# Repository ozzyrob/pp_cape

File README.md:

# pp_cape

Beaglebone Black cape to breakout signals to a 26 pin header

Intent is to replicate order of Parallel Port (not function)
to facilitate migration from x86 Linuxcnc users to BBB Machinekit
users

  * Port 1 header has 8 Outputs + 5 Inputs + 4 Outputs
  * Port 2 header has 8 Inputs + 5 Inputs + 4 Outputs
  * Pin 26 on each header is an "enable pin"
  * I2C is broken out to a 1x4 pin header (SCL SDL 3v3 DGND)
  * P9.1 to P9.10 are broken out to a 2x4 pin header
  * ADC Inputs and ADC ground are broken out (reference has not been)

To be used in conjunction with pp_bob_output & pp_bob_input boards

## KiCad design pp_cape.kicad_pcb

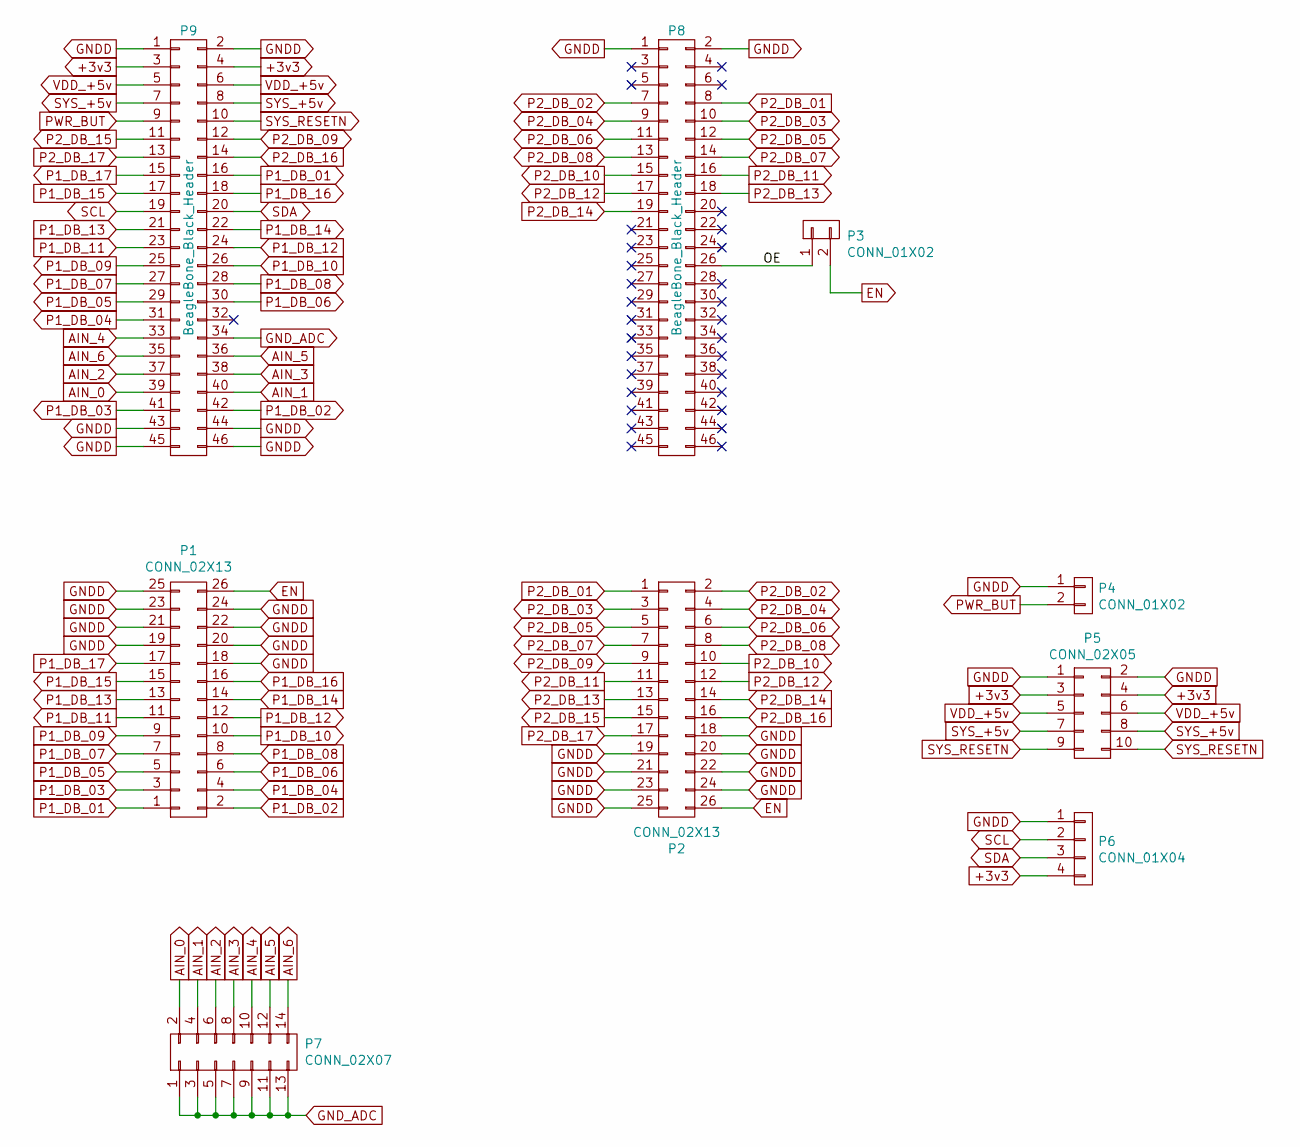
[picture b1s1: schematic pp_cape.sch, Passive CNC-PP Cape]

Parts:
P1, P2: CONN_02X13; Pin_Header_Straight_2x13_Pitch2.54mm
P3, P4: CONN_01X02; Pin_Header_Straight_1x02_Pitch2.54mm
P5: CONN_02X05; Pin_Header_Straight_2x05_Pitch2.54mm
P6: CONN_01X04; Pin_Header_Straight_1x04_Pitch2.54mm
P7: CONN_02X07; Pin_Header_Straight_2x07_Pitch2.54mm
P8, P9: BeagleBone_Black_Header; Socket_BeagleBone_Black

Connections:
+3v3: P5.3, P5.4, P6.4, P9.3, P9.4
/OE: P3.1, P8.26
AIN_0: P7.2, P9.39
AIN_1: P7.4, P9.40
AIN_2: P7.6, P9.37
AIN_3: P7.8, P9.38
AIN_4: P7.10, P9.33
AIN_5: P7.12, P9.36
AIN_6: P7.14, P9.35
EN: P1.26, P2.26, P3.2
GNDD: P1.18, P1.19, P1.20, P1.21, P1.22, P1.23, P1.24, P1.25, P2.18, P2.19, P2.20, P2.21, P2.22, P2.23, P2.24, P2.25, P4.1, P5.1, P5.2, P6.1, P8.1, P8.2, P9.1, P9.2, P9.43, P9.44, P9.45, P9.46
GND_ADC: P7.1, P7.3, P7.5, P7.7, P7.9, P7.11, P7.13, P9.34
P1_DB_01: P1.1, P9.16
P1_DB_02: P1.2, P9.42
P1_DB_03: P1.3, P9.41
P1_DB_04: P1.4, P9.31
P1_DB_05: P1.5, P9.29
P1_DB_06: P1.6, P9.30
P1_DB_07: P1.7, P9.27
P1_DB_08: P1.8, P9.28
P1_DB_09: P1.9, P9.25
P1_DB_10: P1.10, P9.26
P1_DB_11: P1.11, P9.23
P1_DB_12: P1.12, P9.24
P1_DB_13: P1.13, P9.21
P1_DB_14: P1.14, P9.22
P1_DB_15: P1.15, P9.17
P1_DB_16: P1.16, P9.18
P1_DB_17: P1.17, P9.15
P2_DB_01: P2.1, P8.8
P2_DB_02: P2.2, P8.7
P2_DB_03: P2.3, P8.10
P2_DB_04: P2.4, P8.9
P2_DB_05: P2.5, P8.12
P2_DB_06: P2.6, P8.11
P2_DB_07: P2.7, P8.14
P2_DB_08: P2.8, P8.13
P2_DB_09: P2.9, P9.12
P2_DB_10: P2.10, P8.15
P2_DB_11: P2.11, P8.16
P2_DB_12: P2.12, P8.17
P2_DB_13: P2.13, P8.18
P2_DB_14: P2.14, P8.19
P2_DB_15: P2.15, P9.11
P2_DB_16: P2.16, P9.14
P2_DB_17: P2.17, P9.13
PWR_BUT: P4.2, P9.9
SCL: P6.2, P9.19
SDA: P6.3, P9.20
SYS_+5v: P5.7, P5.8, P9.7, P9.8
SYS_RESETN: P5.9, P5.10, P9.10
VDD_+5v: P5.5, P5.6, P9.5, P9.6

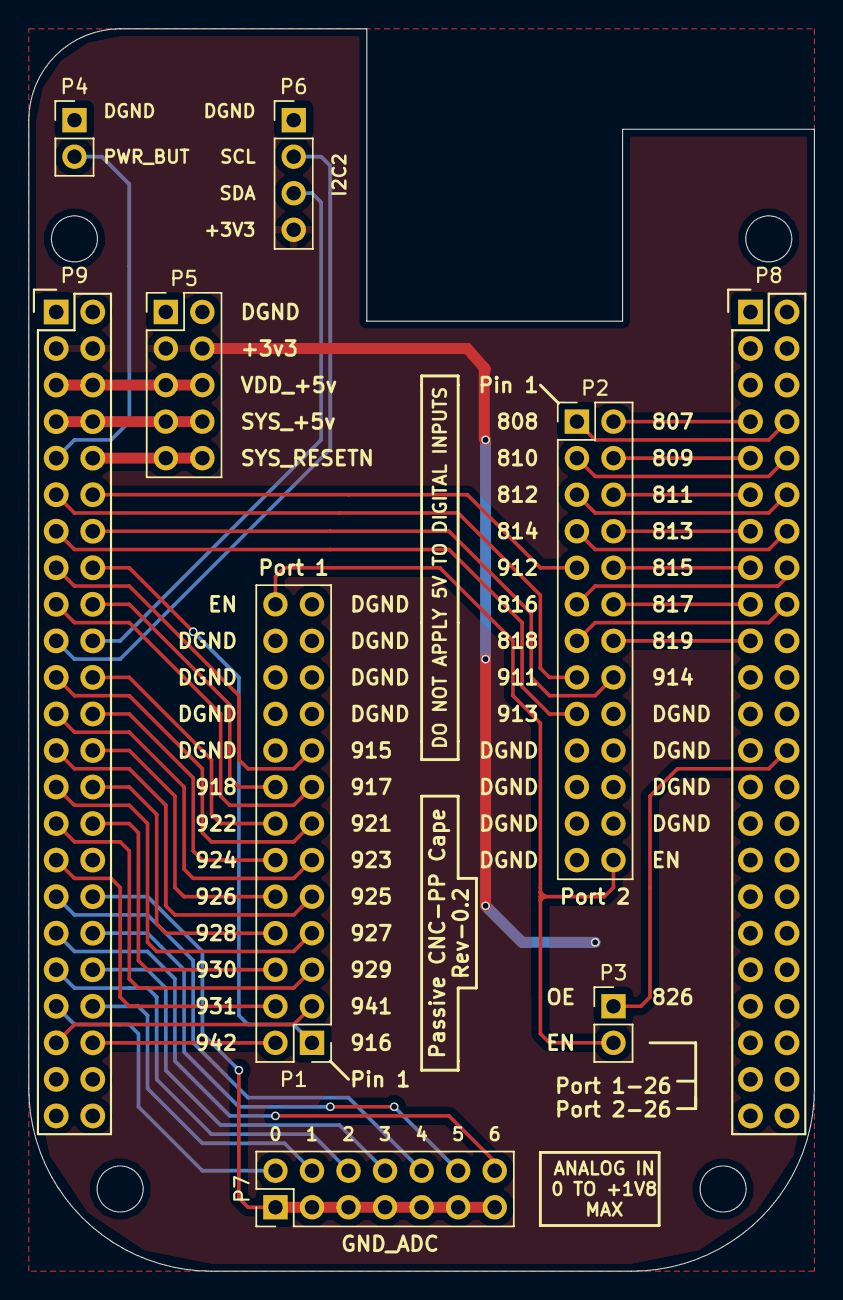
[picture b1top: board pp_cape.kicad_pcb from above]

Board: 2 copper layers, 54.6 x 86.4 mm, 13 parts (0 on the bottom side), 52 nets.

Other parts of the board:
M3, M3#2: MountingHole_3.2mm_M3
mnt1, mnt2: MountingHole_3.2mm_M3

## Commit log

2017-04-19 Initial commit warning ethernet cut out incorrect
2017-04-19 Version V0.3 fixed ethernt cut out amended silkscreen adjusted I2C2 tracks
2017-04-19 Remove *_V02 files
2017-04-19 Renamed files deleting V02 part
2017-04-19 Added Master.txt
2017-04-19 Added V03.txt
2017-07-16 drop -v0.2 from footprints
2017-07-16 hmmmm
2017-07-16 Added board picture and edited Master.txt
2017-07-16 Added V0.2 suffix to manufacture directory to match board verison that was manufactured
2017-07-16 Cleaned up sign off
2017-09-15 Add new directory
2017-09-15 Upload New File
2017-09-20 Update setup.sh change (note) lines
2017-09-20 Update 2-Port-Test.hal
    Chnage from 2xx to 9xx numbering
2017-09-20 Add .gitattribute
2017-09-20 Add spreadsheet showing pin assignments
2017-09-20 Deleted pin assignment spreadsheet form Dcos
2020-03-28 Update README.md
    Stupid me can't English properly
